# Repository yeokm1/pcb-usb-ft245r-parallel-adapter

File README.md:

# pcb-usb-ft245r-parallel-adapter
A USB to parallel adapter using the FTDI FT245R chip. This is not a IEEE 1284 compliant parallel port. Just using the DB25 connector to access the data pins.

##PCB Design software and addons used

1. Kicad 4.0.2 or later

##Images
Not available yet

##Schematic drawings

##Parts required
Not available yet

##References
1. [FTDI library](https://code.launchpad.net/~mrnuke/kicad/ftdi_symlib)

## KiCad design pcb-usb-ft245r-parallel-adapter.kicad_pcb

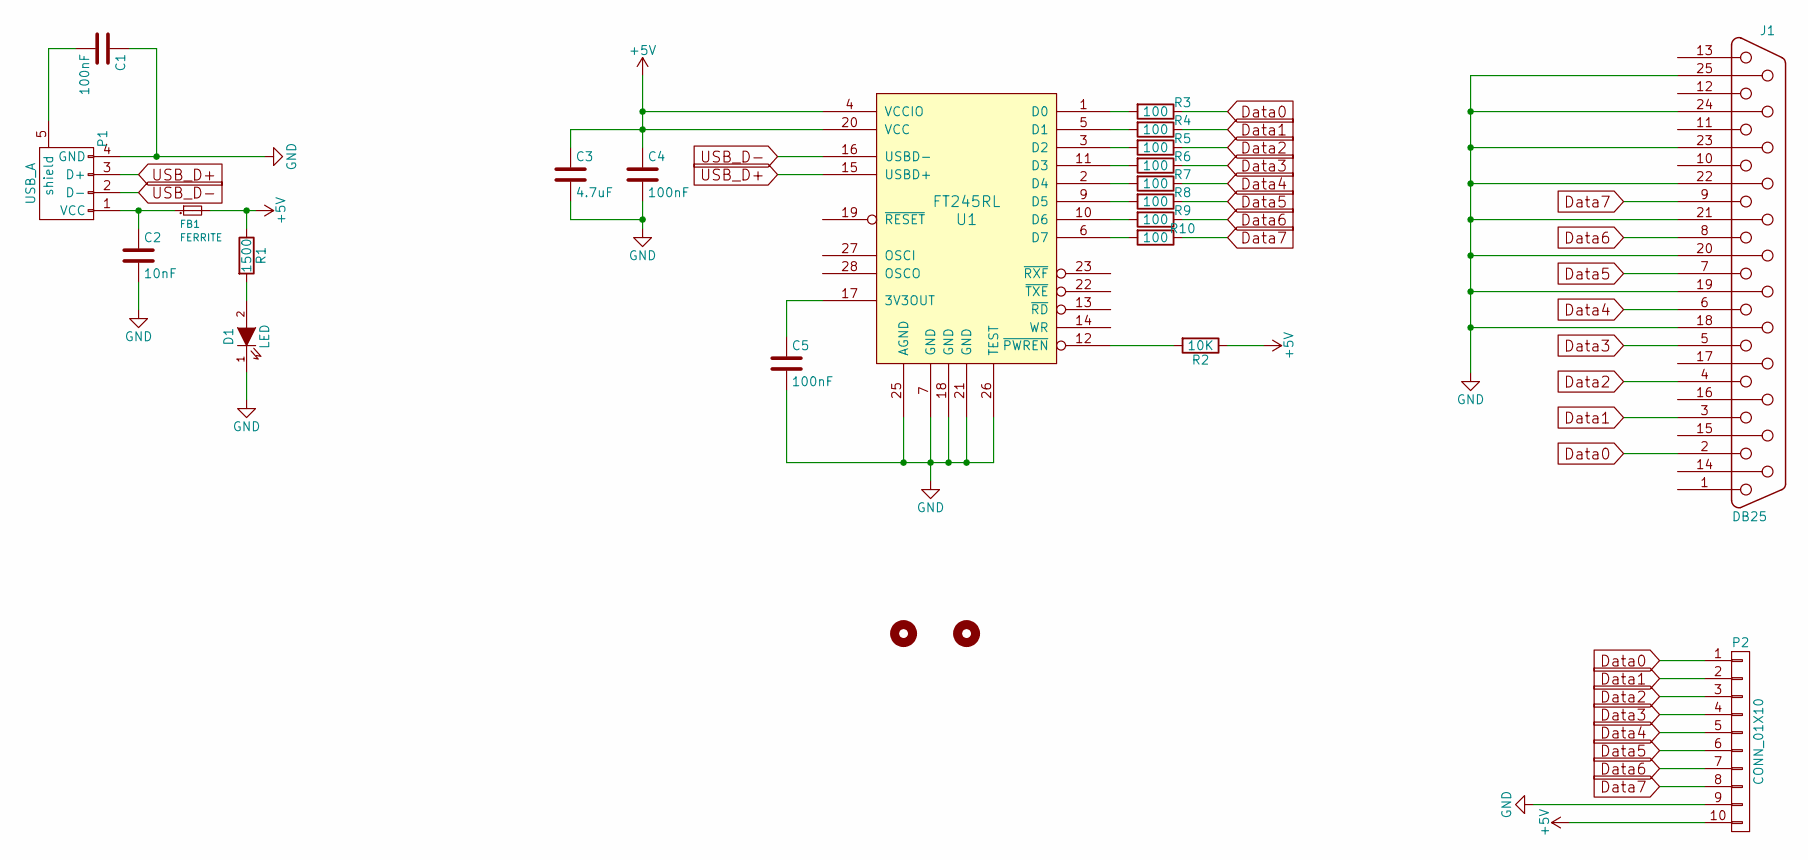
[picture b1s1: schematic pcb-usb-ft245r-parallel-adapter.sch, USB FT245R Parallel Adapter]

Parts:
C1, C4, C5: 100nF; C_0805_HandSoldering
C2: 10nF; C_0805_HandSoldering
C3: 4.7uF; C_0805_HandSoldering
D1: LED; LED_0805
FB1: FERRITE; R_0805_HandSoldering
J1: DB25; DB25FC
MH1, MH2: MOUNTHOLE; HOLE-M3-COND
P1: USB_A
P2: CONN_01X10; Pin_Header_Straight_1x10
R1: 1500; R_0805_HandSoldering
R2: 10K; R_0805_HandSoldering
R3, R4, R5, R6, R7, R8, R9, R10: 100; R_0805_HandSoldering
U1: FT245RL; SSOP-28_5.3x10.2mm_Pitch0.65mm

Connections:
+5V: C3.1, C4.1, FB1.2, P2.10, R1.1, R2.1, U1.4 (VCCIO), U1.20 (VCC)
Data0: J1.2, P2.1, R3.1
Data1: J1.3, P2.2, R4.1
Data2: J1.4, P2.3, R5.1
Data3: J1.5, P2.4, R6.1
Data4: J1.6, P2.5, R7.1
Data5: J1.7, P2.6, R8.1
Data6: J1.8, P2.7, R9.1
Data7: J1.9, P2.8, R10.1
GND: C1.1, C2.2, C3.2, C4.2, C5.2, D1.1 (K), J1.18, J1.19, J1.20, J1.21, J1.22, J1.23, J1.24, J1.25, P1.4 (GND), P2.9, U1.7 (GND), U1.18 (GND), U1.21 (GND), U1.25 (AGND), U1.26 (TEST)
unnamed: C1.2, P1.5 (shield)
unnamed: C2.1, FB1.1, P1.1 (VCC)
unnamed: C5.1, U1.17 (3V3OUT)
unnamed: D1.2 (A), R1.2
unnamed: R2.2, U1.12 (~PWREN)
unnamed: R3.2, U1.1 (D0)
unnamed: R4.2, U1.5 (D1)
unnamed: R5.2, U1.3 (D2)
unnamed: R6.2, U1.11 (D3)
unnamed: R7.2, U1.2 (D4)
unnamed: R8.2, U1.9 (D5)
unnamed: R9.2, U1.10 (D6)
unnamed: R10.2, U1.6 (D7)
USB_D+: P1.3 (D+), U1.15 (USBD+)
USB_D-: P1.2 (D-), U1.16 (USBD-)

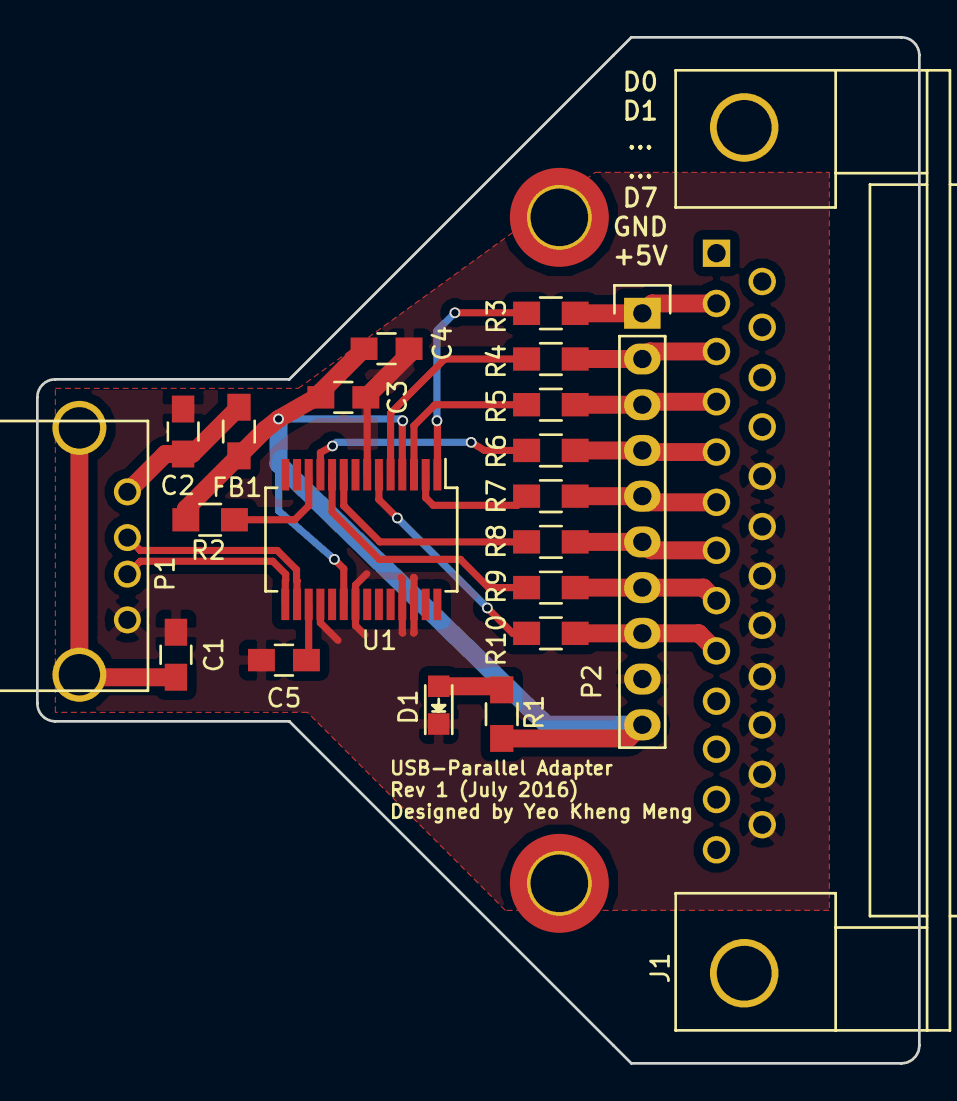
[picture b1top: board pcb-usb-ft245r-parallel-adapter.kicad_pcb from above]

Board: 2 copper layers, 49.0 x 57.0 mm, 23 parts (0 on the bottom side), 25 nets.

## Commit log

2016-07-24 git ignore backup
2016-07-24 replace git ignore
2016-07-24 rev 1 gerber
2016-07-24 versions and images
2016-07-24 schematic
2016-07-24 revert
2016-07-25 add missing libraries
